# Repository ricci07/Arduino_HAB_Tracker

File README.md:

# Arduino_HAB_Tracker
Undergraduate Dissertation HAB Telemetry Development

This is a HAB tracker PCB I am making for my final year project based on information provided by the UKHAS (society)
I am building this from breakout boards, which is not my preferred solution, but it will speed up developement 10-fold (I don't have the time for anything pretty right now)

It features an Arduino UNO (clone), Ublox-M8Q (GPS) Radiometrix NTX2B, BH1750 (light sensor), BMP280 (pressure sensor), ML8511 (UV sensor), MPU-9250 (9 Axis Sensor, 3D acc, 3D GYR, 3D Mag), MS5611 (Super-high alitude sensor), and voltage sensor (this consists of a voltage divider so many be implemented directly)

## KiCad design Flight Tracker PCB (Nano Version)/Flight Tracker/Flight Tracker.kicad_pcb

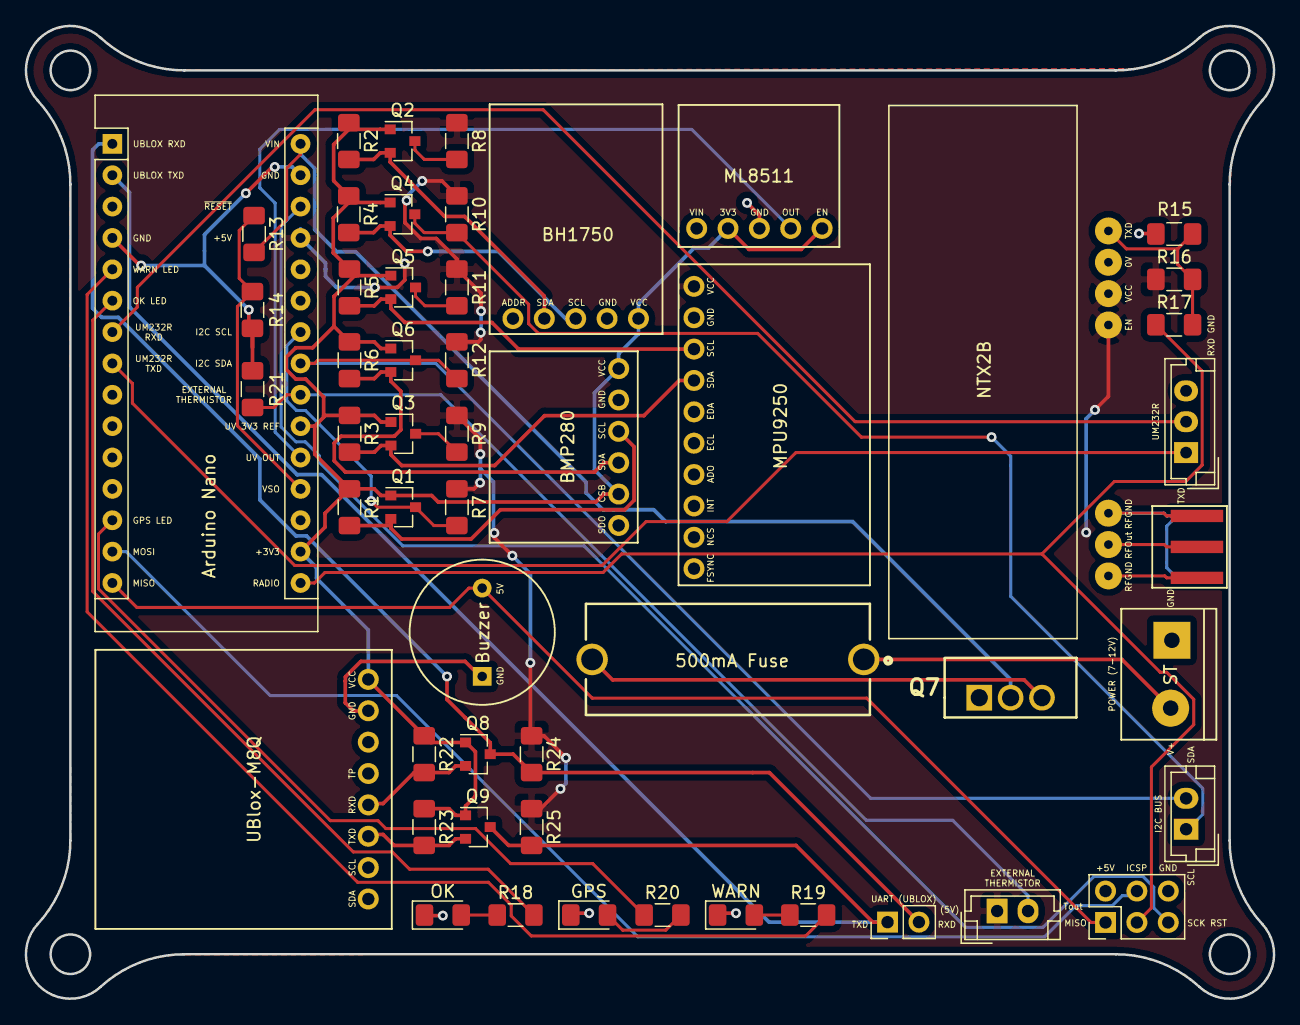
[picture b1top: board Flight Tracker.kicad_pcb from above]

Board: 2 copper layers, 101.1 x 78.8 mm, 53 parts (0 on the bottom side), 40 nets.

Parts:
A1: Arduino_Nano_v3.x; Arduino_Nano_With_Model_Sockets
BZ1: Buzzer; 5V_Buzzer
D1: OK_LED; LED_1206_3216Metric_Pad1.42x1.75mm_HandSolder
D2: GPS_LOCK; LED_1206_3216Metric_Pad1.42x1.75mm_HandSolder
D3: WARN_LED; LED_1206_3216Metric_Pad1.42x1.75mm_HandSolder
F1: 500mA Fuse; MC000827_With_Model
J1, J4: Conn_01x02; JST_EH_B02B-EH-A_1x02_P2.50mm_Vertical
J2: Conn_01x02; PinHeader_1x02_P2.54mm_Vertical
J3: Screw_Terminal_01x02; 2_Pin_Screw_Terminal
J5: Conn_01x03; JST_EH_B03B-EH-A_1x03_P2.50mm_Vertical
J6: Conn_02x03_Odd_Even; PinHeader_2x03_P2.54mm_Vertical
Q1, Q2, Q3, Q4, Q5, Q6, Q8, Q9: BSS138; SOT-23
Q7: FQP47P06; TO254P483X1016X2261-3P
R1, R2, R3, R4, R5, R6, R7, R8, R9, R10, R11, R12, R22, R23, R24, R25: 10K; R_1206_3216Metric_Pad1.42x1.75mm_HandSolder
R13: 30K; R_1206_3216Metric_Pad1.42x1.75mm_HandSolder
R14: 7.5K; R_1206_3216Metric_Pad1.42x1.75mm_HandSolder
R15, R16: 4K7; R_1206_3216Metric_Pad1.42x1.75mm_HandSolder
R17: 47k; R_1206_3216Metric_Pad1.42x1.75mm_HandSolder
R18, R19, R20: 150R; R_1206_3216Metric_Pad1.42x1.75mm_HandSolder
R21: 100k; R_1206_3216Metric_Pad1.42x1.75mm_HandSolder
U1: ML8511_With_Model
U2: BH1750_With_Model
U3: SMA_5pin; SMA_EDGE
U4: NTX2_With_Model
U5: BMP280_With_Model
U6: MPU_9250_With_Model
U7: UBlox_MAX8; ublox_M8Q_with_Model

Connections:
3V3: A1.17, A1.21, Q1.1, Q2.1, Q3.1, Q4.1, Q5.1, Q6.1, Q8.1, Q9.1, R1.1, R2.1, R3.1, R4.1, R5.1, R6.1, R22.1, R23.1, U1.2, U1.5, U2.1, U5.1, U5.5, U7.8
5V: A1.27, J4.1, R7.1, R8.1, R9.1, R10.1, R11.1, R12.1, R16.1, R24.1, R25.1, U4.4, U4.5, U6.1
/I2C_SCL: A1.24, Q1.3, R7.2
/I2C_SDA: A1.23, J1.2, Q6.3, R12.2
/MISO: A1.15, BZ1.1, J6.1
/MOSI: A1.14, J6.4
/RST: A1.28, J6.5
/SCK: A1.16, J6.3, R17.1
/Thermistor: A1.22, J4.2, R21.1
/UM232R_RXD: A1.7, J5.2
/UM232R_TXD: A1.8, J5.1
/UV_OUT: A1.20, U1.4
/V_S_I: A1.30, Q7.2, R13.2
/V_S_O: A1.19, R13.1, R14.1
BH1750_SCL_3V3: Q4.2, R4.2, U2.3
BH1750_SDA_3V3: Q2.2, R2.2, U2.4
BMP280_SCL_3V3: Q1.2, R1.2, U5.3
BMP280_SDA_3V3: Q6.2, R6.2, U5.4
GND: A1.4, A1.29, BZ1.2, D1.1, D2.1, D3.1, J3.2, J5.3, J6.6, Q7.1, R14.2, R15.2, R21.2, U1.3, U2.2, U2.5, U4.6, U5.2, U5.6, U6.2, U6.10, U7.7
MPU9250_SCL_3V3: Q5.2, R5.2, U6.3
MPU9250_SDA_3V3: Q3.2, R3.2, U6.4
unnamed: A1.5, R19.2
unnamed: A1.6, R18.2
unnamed: A1.13, R20.1
unnamed: D1.2, R18.1
unnamed: D2.2, R20.2
unnamed: D3.2, R19.1
unnamed: F1.1, J3.1
unnamed: F1.2, Q7.3
unnamed: J1.1, Q4.3, R10.2
unnamed: Q2.3, R8.2
unnamed: Q3.3, R9.2
unnamed: Q5.3, R11.2
unnamed: R15.1, R16.2, R17.2, U4.7
unnamed: U3.1, U4.2
unnamed: U3.2, U4.1, U4.3
Ublox_RXD_3V3: Q8.2, R22.2, U7.4
Ublox_RXD_5V: A1.1, J2.2, Q8.3, R24.2
Ublox_TXD_3V3: Q9.2, R23.2, U7.3
Ublox_TXD_5V: A1.2, J2.1, Q9.3, R25.2

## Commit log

2020-04-09 initial commit of existing files
2020-04-11 Made a few symbols and footprints for the BH1750, Ublox8, and BMP280
2020-04-11 Created Readme
2020-04-11 Corrected spelling on readme
2020-04-11 Created ML8511, MPU9250_MS5611 symbols and footprints
2020-04-12 Attempted to wire the BMP280 correctly cross referencing the datasheet
2020-04-13 Removed MPU9250+MS5611 and replaced with just MPU9250. Also created voltage sensor used voltage divide to avoid using the pointless breakout board
2020-04-19 Implemented reverse voltage protection at VIN using FQP47P06 (p-channel mosfet with high gate-drain voltage
2020-04-20 Copied the parts list excel document (and updated it with new items) from desktop to laptop
2020-04-21 created footprint for buzzer and corrected it's symbol incorrect wiring
2020-04-29 First bit of good progress on transmitting the NMEA messages parsed using tinyGPS++, also added PUBX commands to turn off unwanted NMEA messages as we only care for GNGGA messages for HAB
2020-05-04 implemented UV sensor, took out carrier shift pot (47k res instead), changed UV_OUT pin, some other stuff, added level shifter for ublox gps tcd and rxd lines, added low voltage detection,\n added no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
2020-05-06 added ICSP header on PCB, added connector for external thermistor with voltage divider to A3, added connector to tap into I2c bus
2020-05-07 created draft pcb, decided that removing the um232r footprint is required to make the pcb look nicer
2020-05-09 Linked Arduino Nano CAD model from grabcad with footprint, created and linked CAD models for ublox GPS, 5V buzzer, and NTX2B
2020-05-09 made bmp280 cad model and linked it to pcb, also created sockets for arduino nano
2020-05-09 Modified a BH1750 CAD model and linked it with footprint
2020-05-10 Created fuse holder and linked it with footprint
